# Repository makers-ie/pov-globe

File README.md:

PoV Globe
=========

Persistence of vision globe project.

Requirements
------------
* Use an FPGA
* The size should be noticable
* Rotation should be well balanced
* Should be easy to interface with from a PC

Design
------
* One ring of LEDs, stuck on a pivoting axis.
* Ring diameter 50 cm is noticable.
* Stepper motor to drive the ring, for speed control.
* Encoder to avoid drifting.
* RGB LEDs
* Stick LEDs on both halves of the ring for better balance.
* Shift LEDs on one half one half-LED for increased resolution.
* Use wireless for interfacing, so we don't have to transfer high-bandwidth data to the rotor.
  * Bluetooth module is suggested.
  * NRF24L01 pair with Teensy USB interface suggested.
* Build PCB ring segments with SMD LEDs mounted on the edge.

Limits
------
* Ring diameter 50 cm; circumference 1.6 m
* PLCC4 RGB LEDs are 3.5x2.8 mm; maximum resolution is 9 dpi
* With interlacing; maximum resolution is 18 dpi
* At 18 dpi, would use 535 LEDs
* Divide circle into **16** sectors, ignore the two bottom sectors
* Each sector has 32 LEDs, for a total of 64 LEDs ignored
* In total, we have **448** LEDs
* Control for RGB needs 1,344 channels
* Spin ring at 60 rps
* We should have the same resolution both horizontally and vertically
* Each slice must update 1,344 channels
* FPGA board has **42** I/O pins
* Divide channels into matrix of 32x42
* With a shift-register column driver, this requires **34** FPGA connections
* Each slice must update 42 columns; FPGA scans at 1.3 MHz
* With RGB555; 32 shades per base color; FPGA runs PWM at **42 MHz**
* With RGB555; framebuffer memory is 572 kB; with double-buffering **1.14 MB**

Mechanical
----------
* A ring divided into 16 sectors, each with a PCB
* Cross-bars horizontally and vertically for rigidity
* Stepper-motor located in center of ring to avoid unbalanced twisting forces
* Plastic fasteners to attach cross-bars to stepper motor and ring PCBs
* Ring PCBs on one side shifted 1/2 LED for interlacing
* Foundation in reinforced concrete with a fixed steel axis extending to the stepper motor
* Steel axis connected to stepper motor with locking pin?
* FPGA board located in the lower part of the ring to utilize the space created by not having LED PCBs there
* Stepper motor driver could be counter-weight for FPGA board
* One (or two?) ball bearings in the lower ring part
* Ball bearings inside copper pipe or plastic to make it easy to fasten the ring PCBs and FPGA
* We can run ground in the fixed steel axis, unless the stepper motor is weird
* If one ball bearing is insulated from the fixed axis, the other pole can go through the bearing
* Hall/optical-sensor for motor auto-calibration (1 pulse/revolution)
* Ring PCBs
  * Copper traces going to the edge, connecting by direct soldering should be rigid and good
  * We will be running MHz signals, so 4-layer PCB is probably needed to have a full ground plane

Electrical
----------
* We should be fine with 5 V
  * FPGA board needs Vcc = 5 V
  * LEDs are Vf <= 3.5 V
  * Stepper motor (42BYGHW609, NEMA 17?) needs 3.4 V (resistive)
* Current usage is max 3 A
  * FPGA likely less than 100 mA
  * LEDs are Ifm < 32*25 mA < 1 A
  * Stepper motor can do 1.7 A (resistive)
* Power usage is max 15 W
* Components
  * Stepper motor driver
  * Power supply 5V/15W
  * Ring sector PCBs x14
  * FPGA interface PCBs x2
    * Ring-side PSU filter
    * Hall/optical-sensor
    * Stepper motor driver
    * LED row drivers
* Each ring PCB will have 32x3 channels
  * With 16 rows, this means 6 columns
  * We split the PCB in two column groups and drive each color as a column, i.e. a 2x3 column configuration
  * Need a 6-bit high-speed shift register, f <= 42 MHz, 23 ns per cycle
  * Prefer ICs that can drive 25 mA LEDs by themselves
  * Candidate is [74VHC595](http://www.fairchildsemi.com/ds/74/74VHC595.pdf), Iout <= 25 mA, Vcc <= 5.5 V, f <= 155 MHz
* FPGA I/O, 48 max
  * 1 Rotation sensor (analog?)
  * 2 LED columns (clock, data)
  * 3 Communications (SPI)
  * 4 Stepper motor output (Bipolar H-bridge)
  * 32 LED rows
  * Max IOH 24 mA when using LVCMOS33 outputs. [Datasheet](http://www.xilinx.com/support/documentation/data_sheets/ds162.pdf), page 10.

Datasheets
----------
These are components which we already have:

* Controller: [Spartan LX9](http://www.xilinx.com/support/documentation/data_sheets/ds160.pdf), 32Mhz oscillator, 48 GPIO pins, 64Mbit SDRAM, 64Mbit Flash
  * [Store](http://store.gadgetfactory.net/papilio-pro)
  * [Pinouts](http://papilio.cc/index.php?n=Playground.PapilioPinouts)
* RGB LED: [PLCC4RGBCT-CA](http://www.hebeiltd.com.cn/led.datasheet/PLCC4RGBCT-CA.pdf)
* RF transceiver: [nRF24L01](http://www.nordicsemi.com/eng/content/download/2726/34069/file/nRF24L01P_Product_Specification_1_0.pdf)
  * [Module](http://www.aliexpress.com/item/2pcs-lot-NRF24L01-2-4GHz-Wireless-Transceiver-Module-for-Arduino-Microcontroller-Free-Shipping/1836172303.html)

Candidates for new parts:

* PSU: [AS-25-5](http://www.aliexpress.com/item/25W-5V-Small-Volume-Single-Output-Switching-power-supply-for-LED-Strip-light/628334432.html)
* PSU: [HR-090505A](http://www.aliexpress.com/item/AC-DC-Adapter-5V-5A-DC-Plug-Size-5-5x2-5mm-Power-Adapter-Charger-Switching-with/1060711434.html)
* Stepper motor: [42BYGHW609](http://www.aliexpress.com/item/Best-Selling-5-PCS-Wantai-4-lead-Nema-17-Stepper-Motor-42BYGHW609-56oz-in-40mm-1/599005546.html)
* Motor driver stage: [L298](http://www.st.com/st-web-ui/static/active/en/resource/technical/document/datasheet/CD00000240.pdf)

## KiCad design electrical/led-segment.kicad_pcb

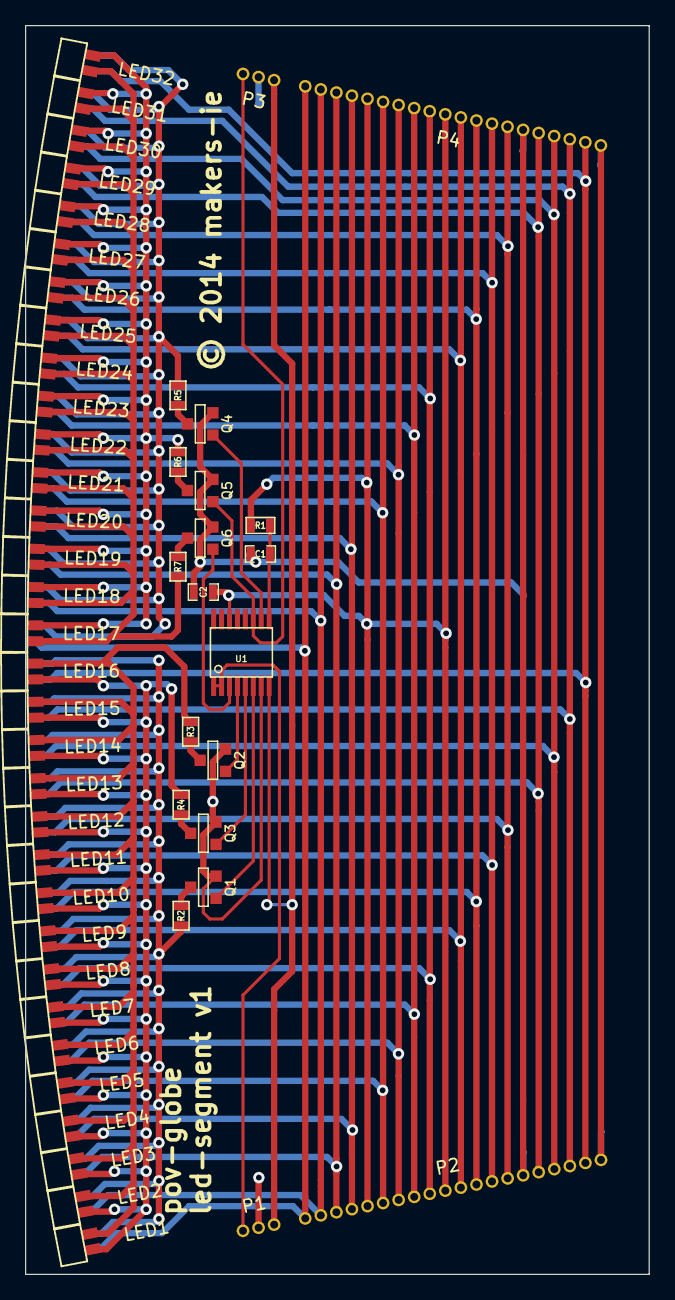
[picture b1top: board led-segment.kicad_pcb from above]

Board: 2 copper layers, 49.9 x 99.9 mm, 52 parts (0 on the bottom side), 39 nets.

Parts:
C1, C2: C; SM0603_Capa
LED1, LED2, LED3, LED4, LED5, LED6, LED7, LED8, LED9, LED10, LED11, LED12, LED13, LED14, LED15, LED16, LED17, LED18, LED19, LED20, LED21, LED22, LED23, LED24, LED25, LED26, LED27, LED28, LED29, LED30, LED31, LED32: PLCC4RGBCT-CA; plcc4-edge
P1, P3: CONN_3; boardedge_3
P2, P4: CONN_20; boardedge_20
Q1, Q2, Q3, Q4, Q5, Q6: FDV301N; SOT23GDS
R1, R2, R3, R4, R5, R6, R7: R; SM0603
U1: 74164; ssop-16

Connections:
+5V: C2.1, P2.5, P2.10, P4.5, P4.10, R1.1, U1.14
/8xLED group A/LCB: LED1.3, LED2.3, LED3.3, LED4.3, LED5.3, LED6.3, LED7.3, LED8.3, LED9.3, LED10.3, LED11.3, LED12.3, LED13.3, LED14.3, LED15.3, LED16.3, R2.1
/8xLED group A/LCG: LED1.4, LED2.4, LED3.4, LED4.4, LED5.4, LED6.4, LED7.4, LED8.4, LED9.4, LED10.4, LED11.4, LED12.4, LED13.4, LED14.4, LED15.4, LED16.4, R3.1
/8xLED group A/LCR: LED1.1, LED2.1, LED3.1, LED4.1, LED5.1, LED6.1, LED7.1, LED8.1, LED9.1, LED10.1, LED11.1, LED12.1, LED13.1, LED14.1, LED15.1, LED16.1, R4.1
/8xLED group C/LCB: LED17.3, LED18.3, LED19.3, LED20.3, LED21.3, LED22.3, LED23.3, LED24.3, LED25.3, LED26.3, LED27.3, LED28.3, LED29.3, LED30.3, LED31.3, LED32.3, R5.1
/8xLED group C/LCG: LED17.4, LED18.4, LED19.4, LED20.4, LED21.4, LED22.4, LED23.4, LED24.4, LED25.4, LED26.4, LED27.4, LED28.4, LED29.4, LED30.4, LED31.4, LED32.4, R6.1
/8xLED group C/LCR: LED17.1, LED18.1, LED19.1, LED20.1, LED21.1, LED22.1, LED23.1, LED24.1, LED25.1, LED26.1, LED27.1, LED28.1, LED29.1, LED30.1, LED31.1, LED32.1, R7.1
/LRA0: LED1.2, LED17.2, P2.1, P4.1
/LRA1: LED2.2, LED18.2, P2.2, P4.2
/LRA2: LED3.2, LED19.2, P2.3, P4.3
/LRA3: LED4.2, LED20.2, P2.4, P4.4
/LRA4: LED5.2, LED21.2, P2.6, P4.6
/LRA5: LED6.2, LED22.2, P2.7, P4.7
/LRA6: LED7.2, LED23.2, P2.8, P4.8
/LRA7: LED8.2, LED24.2, P2.9, P4.9
/LRB0: LED9.2, LED25.2, P2.11, P4.11
/LRB1: LED10.2, LED26.2, P2.12, P4.12
/LRB2: LED11.2, LED27.2, P2.13, P4.13
/LRB3: LED12.2, LED28.2, P2.14, P4.14
/LRB4: LED13.2, LED29.2, P2.16, P4.16
/LRB5: LED14.2, LED30.2, P2.17, P4.17
/LRB6: LED15.2, LED31.2, P2.18, P4.18
/LRB7: LED16.2, LED32.2, P2.19, P4.19
GND: C1.2, C2.2, P1.2, P2.15, P2.20, P3.2, P4.15, P4.20, Q1.S, Q2.S, Q3.S, Q4.S, Q5.S, Q6.S, U1.7
unnamed: C1.1, R1.2, U1.9
unnamed: P1.1, U1.1, U1.2
unnamed: Q3.D, R4.2
unnamed: Q2.D, R3.2
unnamed: Q1.D, R2.2
unnamed: P1.3, P3.3, U1.8
unnamed: Q6.G, U1.3
unnamed: P3.1, Q5.G, U1.11
unnamed: Q4.G, U1.10
unnamed: Q1.G, U1.6
unnamed: Q3.G, U1.5
unnamed: Q2.G, U1.4
unnamed: Q6.D, R7.2
unnamed: Q5.D, R6.2
unnamed: Q4.D, R5.2

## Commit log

2014-06-13 Add initial design thoughts.
2014-06-16 Add datasheets and descriptions of what we currently have as an FPGA board.
2014-06-16 Add initial mechanical model.
    SketchUp for now.
2014-06-16 Add mechanical and electrical design.
2014-06-17 Fill in ring PCB suggestion, stepper motor and PSU datasheets.
2014-06-17 Make proper Papilio Pro mechanical model.
    Also shifts half-ring one half-LED.
    Adds interface boards at the bottom.
2014-06-18 FPGA I/O numbers.
2014-06-18 Add nRF24L01.
2014-06-19 Verilog model of our external 6-bit shift register, a strober that uses that shift register to cycle forever a single bit, and a shader that converts a 5-bit intensity value into a pulse of appropria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
    Not necessary the final design, but useful to get some output for testing
    simulation environment and tooling.
2014-06-22 Add initial electrical schema.
    Uses KiCad. stepper drivers.lib downloaded from www.kicadlib.org/.
2014-06-29 Add LED segment schematic.
2014-07-24 Add genledsegmentpcb.
    A script to place LED modules and generate the board outline
    with good accuracy. The output is meant to be used as a starting
    point for manual modifications.
2014-07-24 Add generated led-segment PCB.
2014-07-24 Add hb.lib and hb.mod.
2014-07-24 Remove Sketchup backup file.
2014-07-24 Small Sketchup fixup.
2014-07-25 Add footprint filter for nrf24l01.
2014-07-25 Split led-segment.sch away from pov-globe.sch.
    They are on separate PCBs and netlist generation is per-schema.
2014-07-25 Add edge connectors to PCB template and fix up LED label alignment.
2014-07-27 Center led-segments PCB in Y direction.
2014-07-29 Add driver transistors to led-segment. Replace 74595.
2014-07-29 Change plcc4rgb pins to passive.
    Fixes ERC warnings.
2014-07-29 Add boardedge connectors.
2014-07-29 Fix boardedge_20 pad 1 position.
2014-07-29 Add led-segment.cmp.
2014-07-29 Fix ERC warnings for led-segment.
2014-07-29 Add led-segment decoupling capacitor. Rewire for PCB layout.
    Rewire transistors to have a better PCB layout.
2014-07-29 Route led-segment board.
    Should be complete now.
2014-07-29 Change led-segments PCB to A4.
2014-07-30 Change places of p3 and p20 connectors.
    We need more space for the column driver IC.
    Fix pad 1 on p20.
2014-07-30 Enlarge boardedge pads. Small track fixups.
2014-09-14 Add led-segment ground plane. Convert to two layer.
2014-09-14 Add hb.dcm.
2014-09-14 Ignore Kicad backup files.
2014-09-21 Move led-segment text to silk screen. Add 50x100 mm edge cut.
2014-09-21 Add prod/led-segment.zip. Version 1 for seeedstudio.
2014-09-21 Increase all vias to 36/20 mil mil.
2014-10-19 Add FPGA output current data.

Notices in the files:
electrical/led-segment.kicad_pcb:
© 2014 makers-ie
